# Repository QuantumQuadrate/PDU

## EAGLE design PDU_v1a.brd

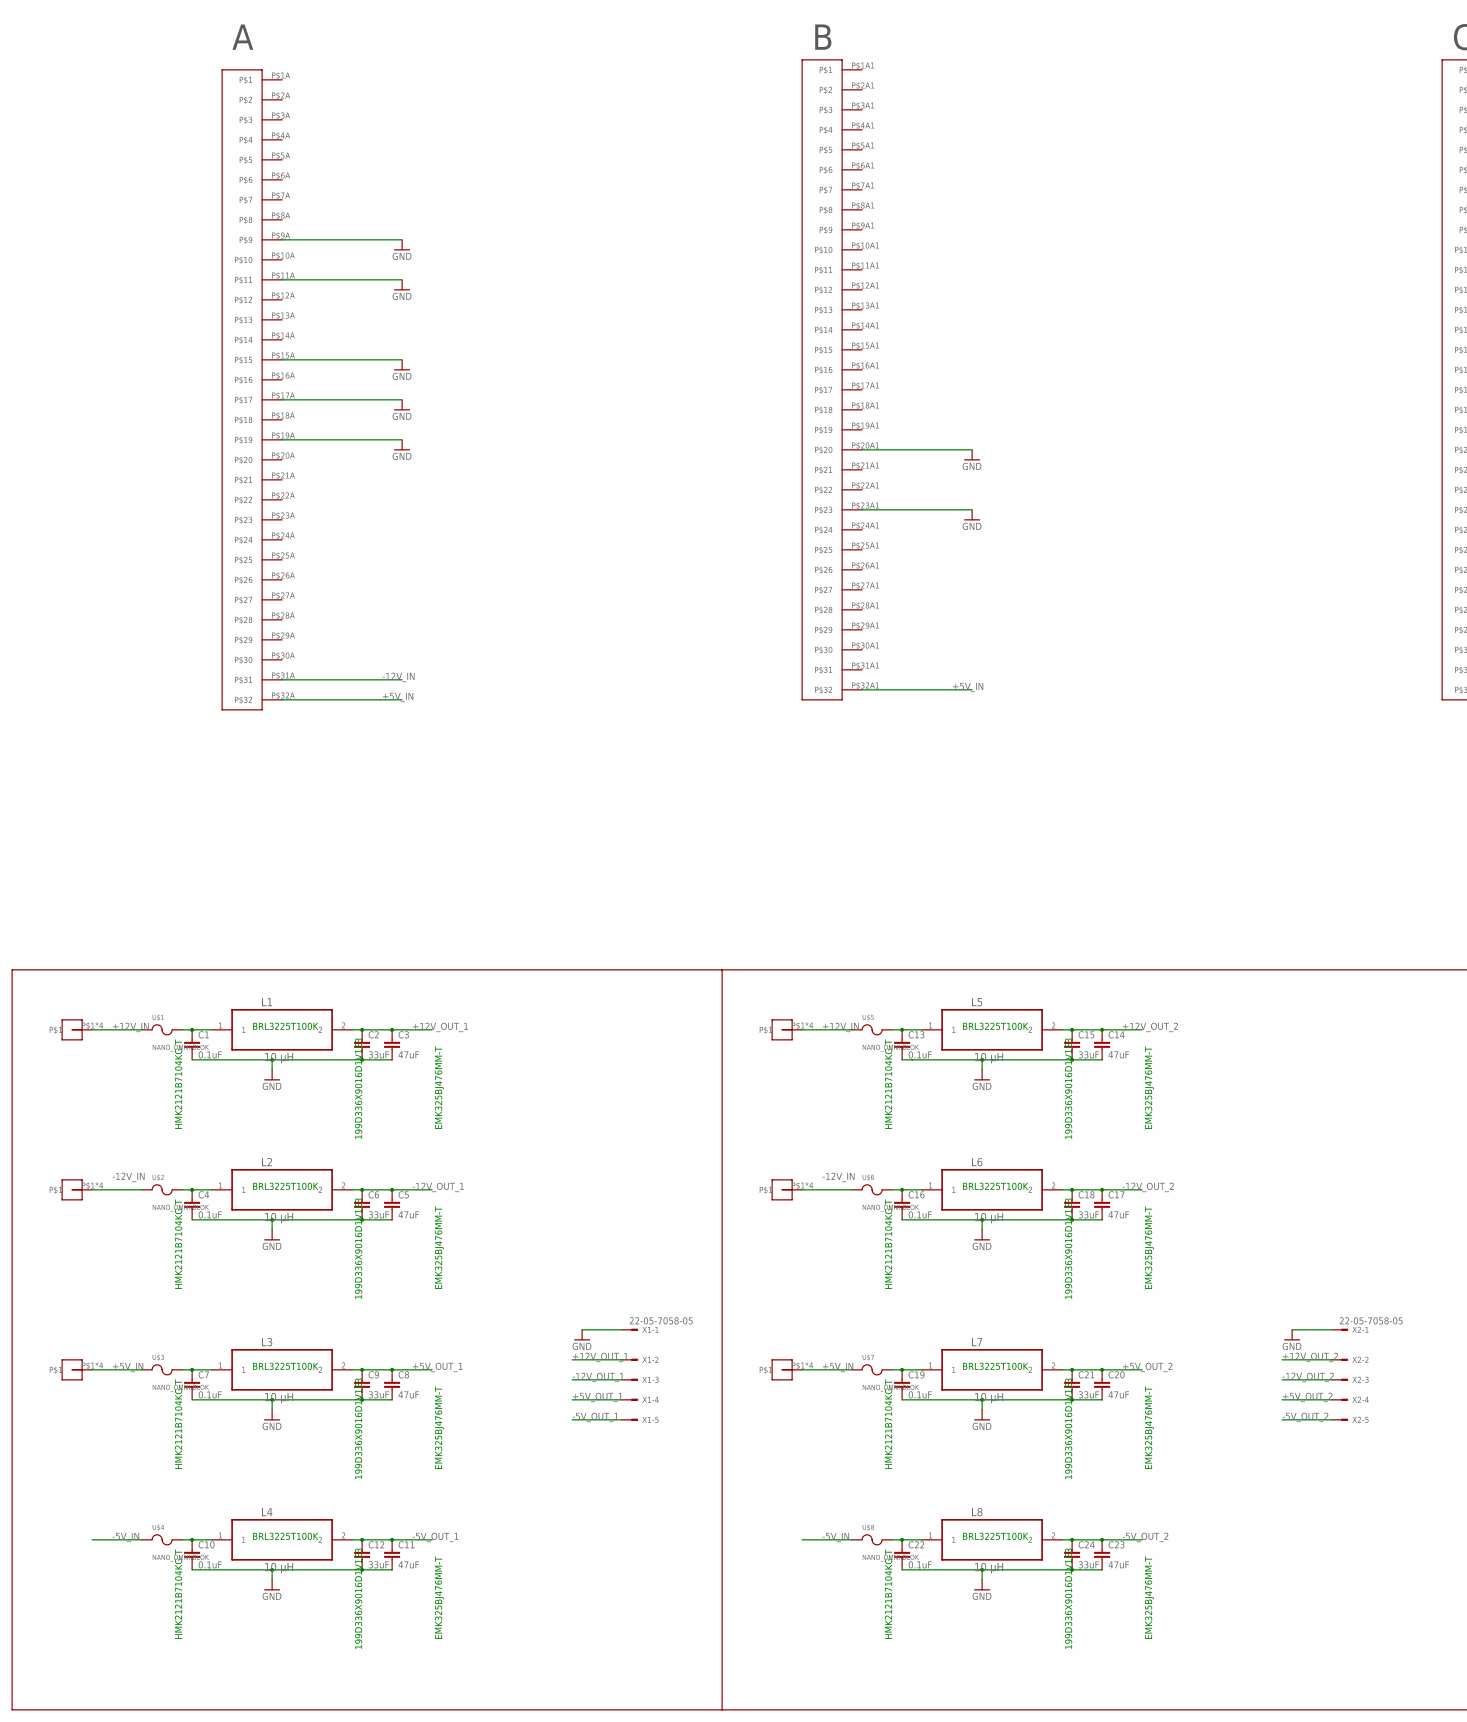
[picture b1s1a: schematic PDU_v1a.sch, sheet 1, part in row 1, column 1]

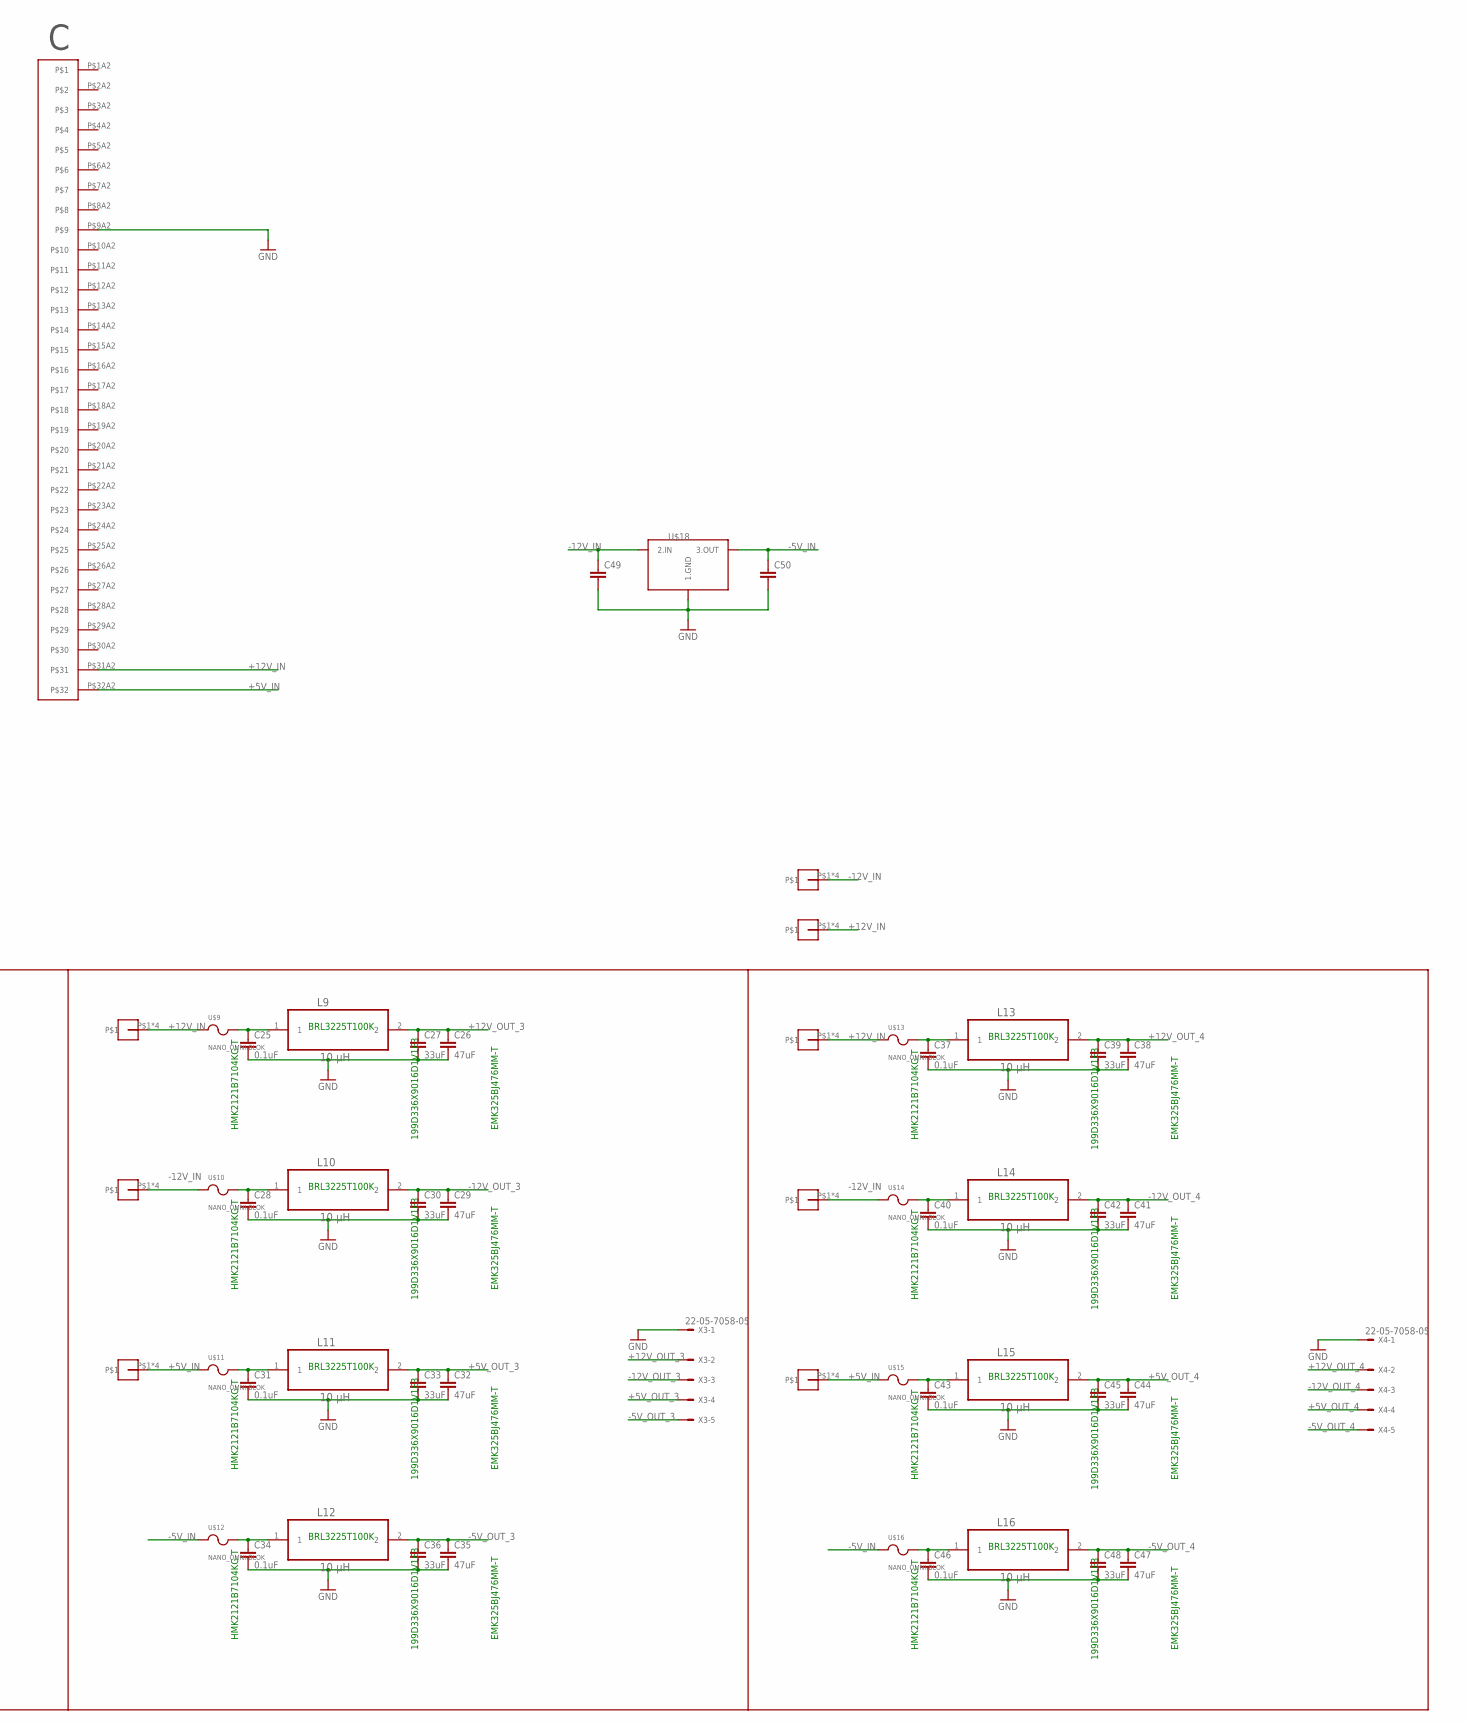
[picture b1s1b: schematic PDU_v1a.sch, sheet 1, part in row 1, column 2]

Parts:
+5V, +5V1, +5V2, +5V3, +12V, +12V1, +12V2, +12V3, +12V4: POWERTAP-7691; KEYSTONE7691
-12V, -12V1, -12V2, -12V3, -12V4: POWERTAP-7691; KEYSTONE7691
C1, C4, C7, C10, C13, C16, C19, C22, C25, C28, C31, C34, C37, C40, C43, C46: 0.1uF; C0805
C2, C6, C9, C12, C15, C18, C21, C24, C27, C30, C33, C36, C39, C42, C45, C48: 33uF; C025-025X050
C3, C5, C8, C11, C14, C17, C20, C23, C26, C29, C32, C35, C38, C41, C44, C47: 47uF; C1210
C49, C50: C-EUC0805; C0805
L1, L2, L3, L4, L5, L6, L7, L8, L9, L10, L11, L12, L13, L14, L15, L16: 10 µH; INDC3225X240N
U$1, U$2, U$3, U$4, U$5, U$6, U$7, U$8, U$9, U$10, U$11, U$12, U$13, U$14, U$15, U$16: NANO_OMNI-BLOK; NANO2-OMNI-BLOK
U$17: DIN_41612_PLUG
U$18: LM2990; TO-263-3
X1, X2, X3, X4: 22-05-7058-05; 7395-05

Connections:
+5V_1: C7.1, L3.1, U$3.P$2
+5V_2: C19.1, L7.1, U$7.P$2
+5V_3: C31.1, L11.1, U$11.P$2
+5V_4: C43.1, L15.1, U$15.P$2
+5V_IN: +5V.P$1, +5V.P$2, +5V.P$3, +5V.P$4, +5V1.P$1, +5V1.P$2, +5V1.P$3, +5V1.P$4, +5V2.P$1, +5V2.P$2, +5V2.P$3, +5V2.P$4, +5V3.P$1, +5V3.P$2, +5V3.P$3, +5V3.P$4, U$3.P$1, U$7.P$1, U$11.P$1, U$15.P$1, U$17.P$32A, U$17.P$32A1, U$17.P$32A2
+5V_OUT_1: C8.1, C9.1, L3.2, X1.4
+5V_OUT_2: C20.1, C21.1, L7.2, X2.4
+5V_OUT_3: C32.1, C33.1, L11.2, X3.4
+5V_OUT_4: C44.1, C45.1, L15.2, X4.4
+12V_1: C1.1, L1.1, U$1.P$2
+12V_2: C13.1, L5.1, U$5.P$2
+12V_3: C25.1, L9.1, U$9.P$2
+12V_4: C37.1, L13.1, U$13.P$2
+12V_IN: +12V.P$1, +12V.P$2, +12V.P$3, +12V.P$4, +12V1.P$1, +12V1.P$2, +12V1.P$3, +12V1.P$4, +12V2.P$1, +12V2.P$2, +12V2.P$3, +12V2.P$4, +12V3.P$1, +12V3.P$2, +12V3.P$3, +12V3.P$4, +12V4.P$1, +12V4.P$2, +12V4.P$3, +12V4.P$4, U$1.P$1, U$5.P$1, U$9.P$1, U$13.P$1, U$17.P$31A2
+12V_OUT_1: C2.1, C3.1, L1.2, X1.2
+12V_OUT_2: C14.1, C15.1, L5.2, X2.2
+12V_OUT_3: C26.1, C27.1, L9.2, X3.2
+12V_OUT_4: C38.1, C39.1, L13.2, X4.2
-5V_1: C10.1, L4.1, U$4.P$2
-5V_2: C22.1, L8.1, U$8.P$2
-5V_3: C34.1, L12.1, U$12.P$2
-5V_4: C46.1, L16.1, U$16.P$2
-5V_IN: C50.1, U$4.P$1, U$8.P$1, U$12.P$1, U$16.P$1, U$18.P$3 (3.OUT)
-5V_OUT_1: C11.1, C12.1, L4.2, X1.5
-5V_OUT_2: C23.1, C24.1, L8.2, X2.5
-5V_OUT_3: C35.1, C36.1, L12.2, X3.5
-5V_OUT_4: C47.1, C48.1, L16.2, X4.5
-12V_1: C4.1, L2.1, U$2.P$2
-12V_2: C16.1, L6.1, U$6.P$2
-12V_3: C28.1, L10.1, U$10.P$2
-12V_4: C40.1, L14.1, U$14.P$2
-12V_IN: -12V.P$1, -12V.P$2, -12V.P$3, -12V.P$4, -12V1.P$1, -12V1.P$2, -12V1.P$3, -12V1.P$4, -12V2.P$1, -12V2.P$2, -12V2.P$3, -12V2.P$4, -12V3.P$1, -12V3.P$2, -12V3.P$3, -12V3.P$4, -12V4.P$1, -12V4.P$2, -12V4.P$3, -12V4.P$4, C49.1, U$2.P$1, U$6.P$1, U$10.P$1, U$14.P$1, U$17.P$31A, U$18.P$2 (2.IN), U$18.P$4 (2.IN)
-12V_OUT_1: C5.1, C6.1, L2.2, X1.3
-12V_OUT_2: C17.1, C18.1, L6.2, X2.3
-12V_OUT_3: C29.1, C30.1, L10.2, X3.3
-12V_OUT_4: C41.1, C42.1, L14.2, X4.3
GND: C1.2, C2.2, C3.2, C4.2, C5.2, C6.2, C7.2, C8.2, C9.2, C10.2, C11.2, C12.2, C13.2, C14.2, C15.2, C16.2, C17.2, C18.2, C19.2, C20.2, C21.2, C22.2, C23.2, C24.2, C25.2, C26.2, C27.2, C28.2, C29.2, C30.2, C31.2, C32.2, C33.2, C34.2, C35.2, C36.2, C37.2, C38.2, C39.2, C40.2, C41.2, C42.2, C43.2, C44.2, C45.2, C46.2, C47.2, C48.2, C49.2, C50.2, U$17.P$9A, U$17.P$9A2, U$17.P$11A, U$17.P$15A, U$17.P$17A, U$17.P$19A, U$17.P$20A1, U$17.P$23A1, U$18.P$1 (1.GND), X1.1, X2.1, X3.1, X4.1

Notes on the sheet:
HMK2121B7104KG-T
EMK325BJ476MM-T
199D336X9016D1V1E3
BRL3225T100K

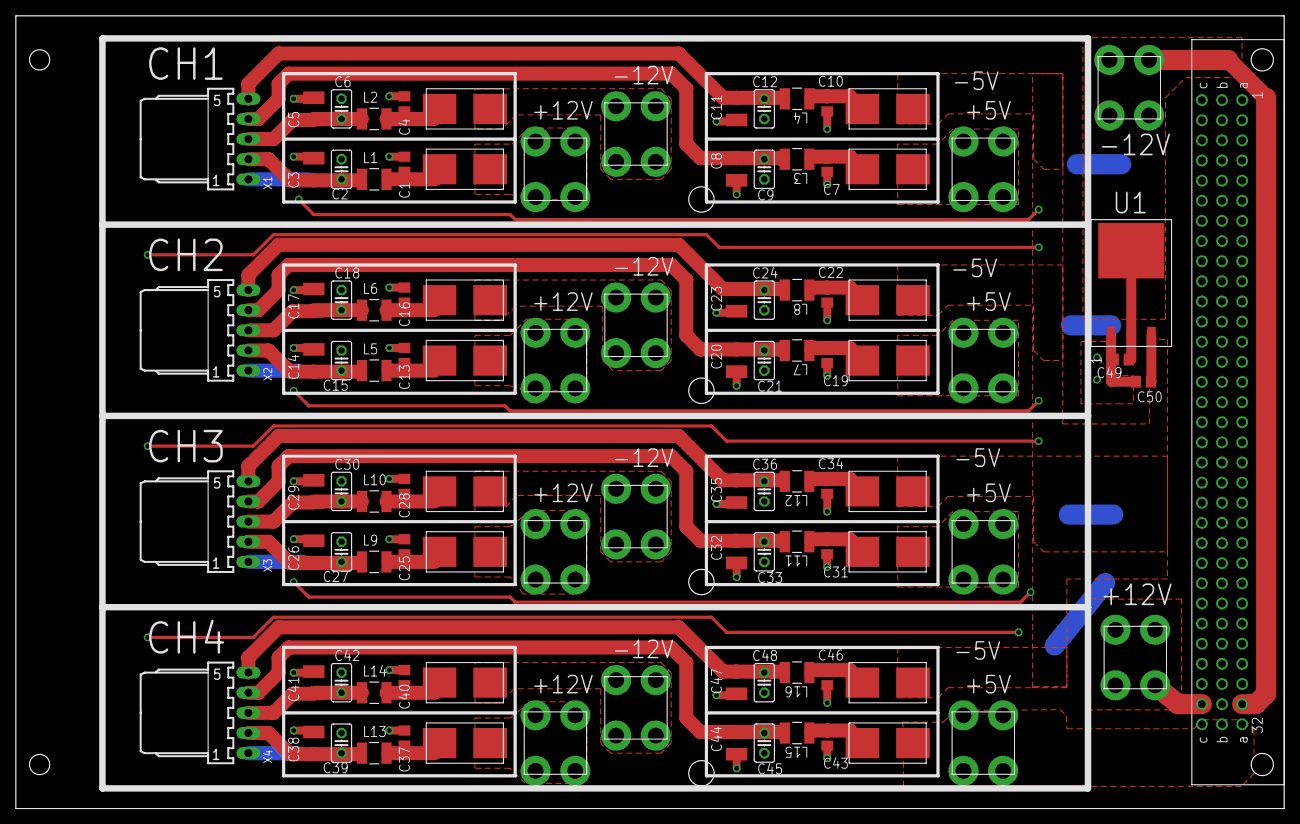
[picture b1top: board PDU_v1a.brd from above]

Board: 2 copper layers, 160.0 x 100.0 mm, 102 parts (0 on the bottom side), 37 nets.

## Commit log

2017-04-20 Initial commit of PDU_v1b
